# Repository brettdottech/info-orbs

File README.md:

# Info Orbs — Widget Expansion (Simon Geiger's fork)

This is a personal fork of [brettdottech/info-orbs](https://github.com/brettdottech/info-orbs), an open source ESP32-based desk display with five round TFT screens ("orbs"). This fork adds new widgets on top of the upstream project — currently a **Calendar widget** (see below).

> This fork isn't affiliated with or supported by the upstream project's Discord/community — please only reach out there for questions about the base hardware/firmware, not for issues specific to the widgets added here.

## Getting the hardware & base setup

This fork doesn't change the hardware or the base setup process, so refer to the upstream project for all of that:

- [Get a Dev Kit](https://brett.tech/collections/electronics-projects/products/info-orbs-full-dev-kit) — all the parts you need, pre-picked.
- [Firmware Install / Flashing Guide](references/Firmware%20Install%20Guide.md) and [YouTube assembly/flashing walkthrough](https://link.brett.tech/orbsYT).
- [Upstream README](https://github.com/brettdottech/info-orbs) — wiring diagram, dev environment (PlatformIO) setup, and the full list of existing widgets (clock, weather, stocks, MQTT, parqet.com, custom web data) and their configuration.
- [Discord](https://link.brett.tech/discord) for general project support and community.

Once you have the base project cloned, built, and flashing successfully (per the guides above), come back here for the widgets this fork adds.

## Calendar Widget

Shows your calendar right on the orbs: a clock, a month-at-a-glance grid, and an agenda of upcoming events — synced from any calendar that can publish a standard `.ics` feed (Google Calendar, Outlook/Microsoft 365, iCloud, etc.).

<!-- TODO: add a photo of the calendar widget in action -->

**What it brings you:**
- **Orb 1 — Clock.** Reuses the existing clock widget.
- **Orb 2 — Month grid.** Current month, today highlighted, with an indicator showing how long ago the calendar last synced.
- **Orbs 3–5 — Agenda**, toggleable between two modes:
  - *Next 3 events* — your next few upcoming events, title + time.
  - *Next 3 days* — a day-by-day view of what's coming up, several events per day.
  - An event that's currently happening is highlighted with a ring so it's obvious at a glance.
- Recurring events are supported (daily/weekly/monthly/yearly patterns, including things like "2nd Wednesday of the month"), including individually-rescheduled or cancelled occurrences.
- Declined and cancelled events are automatically filtered out.
- Calendars authored in a different timezone than your device convert correctly for a curated set of common named timezones (see limitations below).

**Setup:**
1. Get a secret `.ics` URL from your calendar provider (in Google Calendar: Settings → your calendar → "Secret address in iCal format"; Outlook: Settings → Shared calendars → "Publish a calendar"). Treat this URL like a password — anyone with it can read your calendar.
2. In `firmware/config/config.h` (see the upstream setup guide for how to create this file from `config.h.template`), set:
   ```c
   #define CALENDAR_ICS_URL "https://your-calendar-provider.example/your-secret-feed.ics"
   ```
3. Optionally raise `CALENDAR_MAX_EVENTS` (default 40) if you have a busy calendar and want more upcoming events kept in memory:
   ```c
   #define CALENDAR_MAX_EVENTS 80
   ```
4. Flash as usual. The calendar syncs automatically at boot and every hour after that.

**Using it:**
- Middle short press — switch between page 1/2 of the current agenda mode.
- Middle medium press — switch orbs 3–5 between "Next 3 events" and "Next 3 days".
- Middle long press — force an immediate re-sync of the calendar.
- Left/right — cycle to other widgets, same as everywhere else.

**Known limitations:** 
- a single `.ics` source at a time; 
- timezones are handled correctly for a curated list of common named zones (not full `VTIMEZONE`-block parsing — see [ADR-001](docs/adr/ADR-001-calendar-widget.md) for the exact scope and rationale, and for anyone wanting the full technical design behind this widget). 
- only been verified against Google Calendar and Outlook/Microsoft 365 `.ics` feeds so far — feedback on other providers (iCloud, etc.) is very welcome.

## Changelog

Notable changes in this fork (current version: **1.2.0**) are tracked in [CHANGELOG.md](CHANGELOG.md).

## License

This project (including this fork's additions) is licensed under AGPLv3 — see [LICENSE.txt](LICENSE.txt).

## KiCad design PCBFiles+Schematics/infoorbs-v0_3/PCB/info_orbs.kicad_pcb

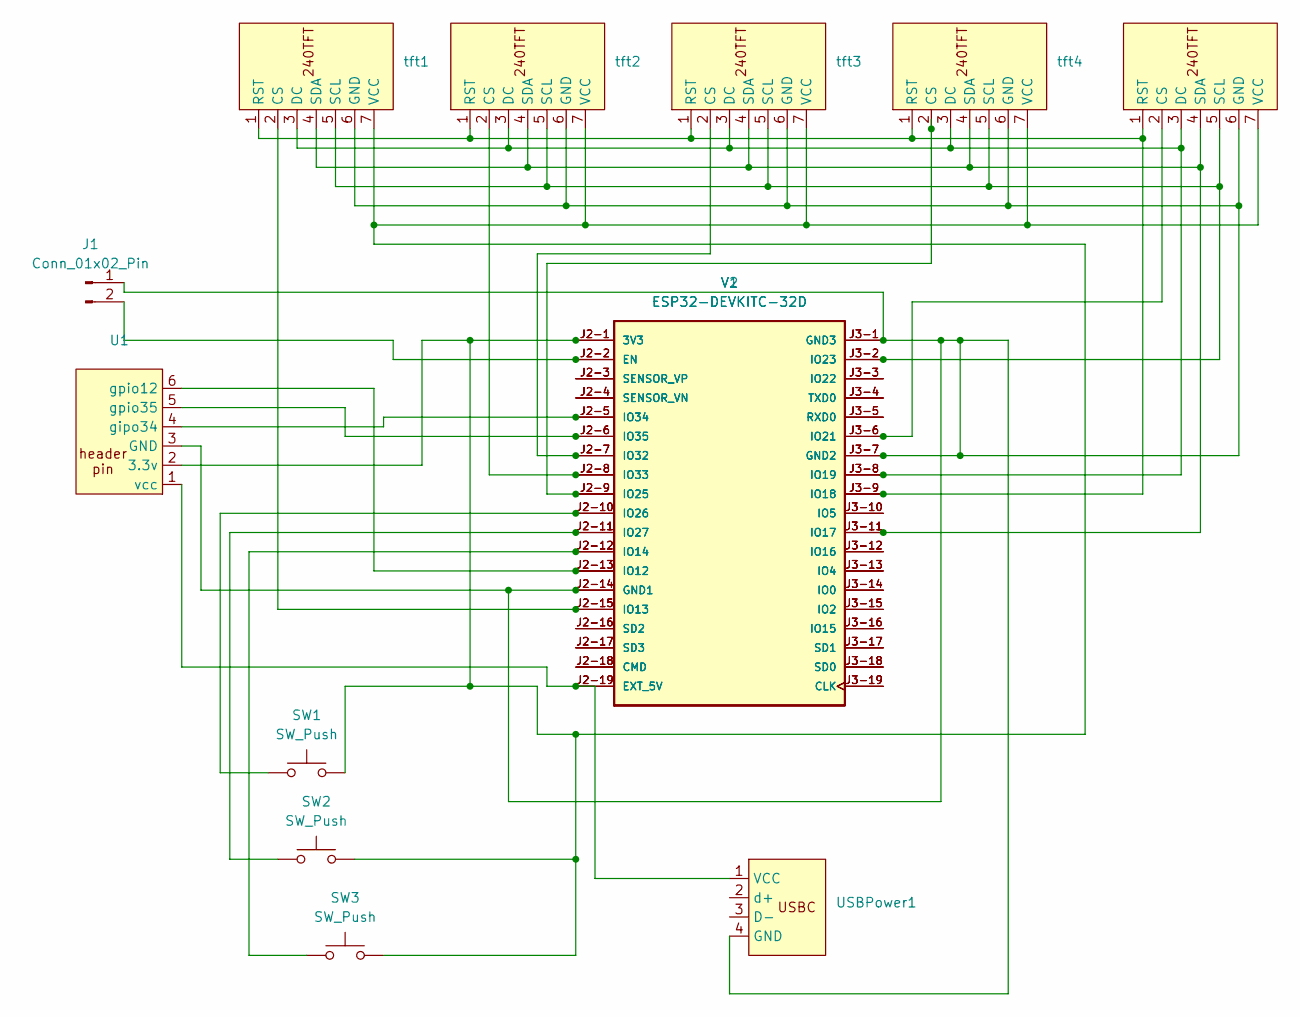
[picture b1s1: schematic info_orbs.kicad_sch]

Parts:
J1: Conn_01x02_Pin; PinHeader_1x02_P2.54mm_Vertical
SW1, SW2, SW3: SW_Push; SW_PUSH_6mm_H5mm
U1: PinHeader_1x06_P2.54mm_Vertical
USBPower1: PinHeader_1x04_P2.54mm_Vertical
V1: ESP32-DEVKITC-32D; 38 Pin Board; PARTREV V4
V2: ESP32-DEVKITC-32D; 38 Pin Board thin; PARTREV V4
tft1, tft2, tft3, tft4, tft5: PinHeader_1x07_P2.54mm_Vertical

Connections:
unnamed: J1.1, U1.3 (GND), USBPower1.4 (GND), V1.J2-14 (GND1), V1.J3-1 (GND3), V1.J3-7 (GND2), V2.J2-14 (GND1), V2.J3-1 (GND3), V2.J3-7 (GND2), tft1.6 (GND), tft2.6 (GND), tft3.6 (GND), tft4.6 (GND), tft5.6 (GND)
unnamed: J1.2, V1.J2-2 (EN), V2.J2-2 (EN)
unnamed: SW1.2, SW2.2, SW3.2, U1.2 (3.3v), V1.J2-1 (3V3), V2.J2-1 (3V3), tft1.7 (VCC), tft2.7 (VCC), tft3.7 (VCC), tft4.7 (VCC), tft5.7 (VCC)
unnamed: U1.4 (gipo34), V1.J2-5 (IO34), V2.J2-5 (IO34)
unnamed: U1.6 (gpio12), V1.J2-13 (IO12), V2.J2-13 (IO12)
unnamed: U1.5 (gpio35), V1.J2-6 (IO35), V2.J2-6 (IO35)
unnamed: U1.1 (vcc), USBPower1.1 (VCC), V1.J2-19 (EXT_5V), V2.J2-19 (EXT_5V)
unnamed: V1.J3-19 (CLK), V2.J3-19 (CLK)
unnamed: V1.J2-18 (CMD), V2.J2-18 (CMD)
unnamed: V1.J3-14 (IO0), V2.J3-14 (IO0)
unnamed: V1.J3-15 (IO2), V2.J3-15 (IO2)
unnamed: V1.J3-13 (IO4), V2.J3-13 (IO4)
unnamed: V1.J3-10 (IO5), V2.J3-10 (IO5)
unnamed: V1.J2-15 (IO13), V2.J2-15 (IO13), tft1.2 (CS)
unnamed: SW3.1, V1.J2-12 (IO14), V2.J2-12 (IO14)
unnamed: V1.J3-16 (IO15), V2.J3-16 (IO15)
unnamed: V1.J3-12 (IO16), V2.J3-12 (IO16)
unnamed: V1.J3-11 (IO17), V2.J3-11 (IO17), tft1.4 (SDA), tft2.4 (SDA), tft3.4 (SDA), tft4.4 (SDA), tft5.4 (SDA)
unnamed: V1.J3-9 (IO18), V2.J3-9 (IO18), tft1.1 (RST), tft2.1 (RST), tft3.1 (RST), tft4.1 (RST), tft5.1 (RST)
unnamed: V1.J3-8 (IO19), V2.J3-8 (IO19), tft1.3 (DC), tft2.3 (DC), tft3.3 (DC), tft4.3 (DC), tft5.3 (DC)
unnamed: V1.J3-6 (IO21), V2.J3-6 (IO21), tft5.2 (CS)
unnamed: V1.J3-3 (IO22), V2.J3-3 (IO22)
unnamed: V1.J3-2 (IO23), V2.J3-2 (IO23), tft1.5 (SCL), tft2.5 (SCL), tft3.5 (SCL), tft4.5 (SCL), tft5.5 (SCL)
unnamed: V1.J2-9 (IO25), V2.J2-9 (IO25), tft4.2 (CS)
unnamed: SW1.1, V1.J2-10 (IO26), V2.J2-10 (IO26)
unnamed: SW2.1, V1.J2-11 (IO27), V2.J2-11 (IO27)
unnamed: V1.J2-7 (IO32), V2.J2-7 (IO32), tft3.2 (CS)
unnamed: V1.J2-8 (IO33), V2.J2-8 (IO33), tft2.2 (CS)
unnamed: V1.J3-5 (RXD0), V2.J3-5 (RXD0)
unnamed: V1.J3-18 (SD0), V2.J3-18 (SD0)
unnamed: V1.J3-17 (SD1), V2.J3-17 (SD1)
unnamed: V1.J2-16 (SD2), V2.J2-16 (SD2)
unnamed: V1.J2-17 (SD3), V2.J2-17 (SD3)
unnamed: V1.J2-4 (SENSOR_VN), V2.J2-4 (SENSOR_VN)
unnamed: V1.J2-3 (SENSOR_VP), V2.J2-3 (SENSOR_VP)
unnamed: V1.J3-4 (TXD0), V2.J3-4 (TXD0)

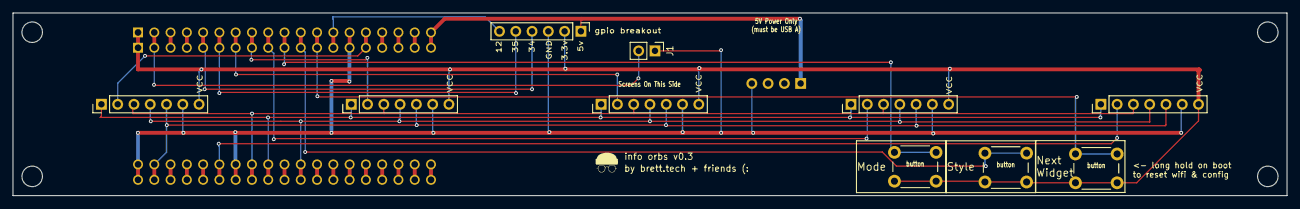
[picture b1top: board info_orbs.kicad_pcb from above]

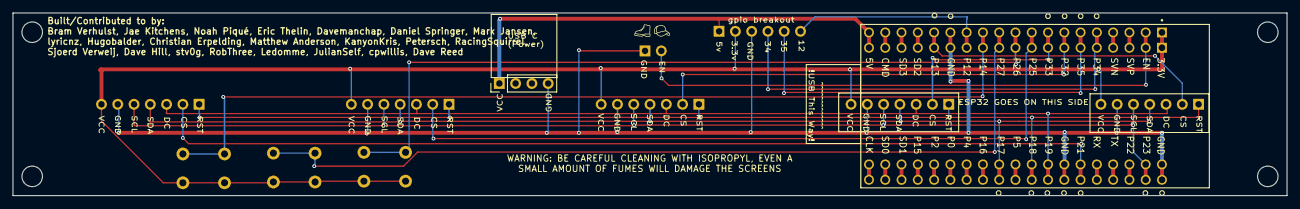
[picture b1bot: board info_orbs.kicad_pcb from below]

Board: 2 copper layers, 198.8 x 28.5 mm, 14 parts (3 on the bottom side), 36 nets.

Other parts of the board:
G*: LOGO; beaniegraphioc

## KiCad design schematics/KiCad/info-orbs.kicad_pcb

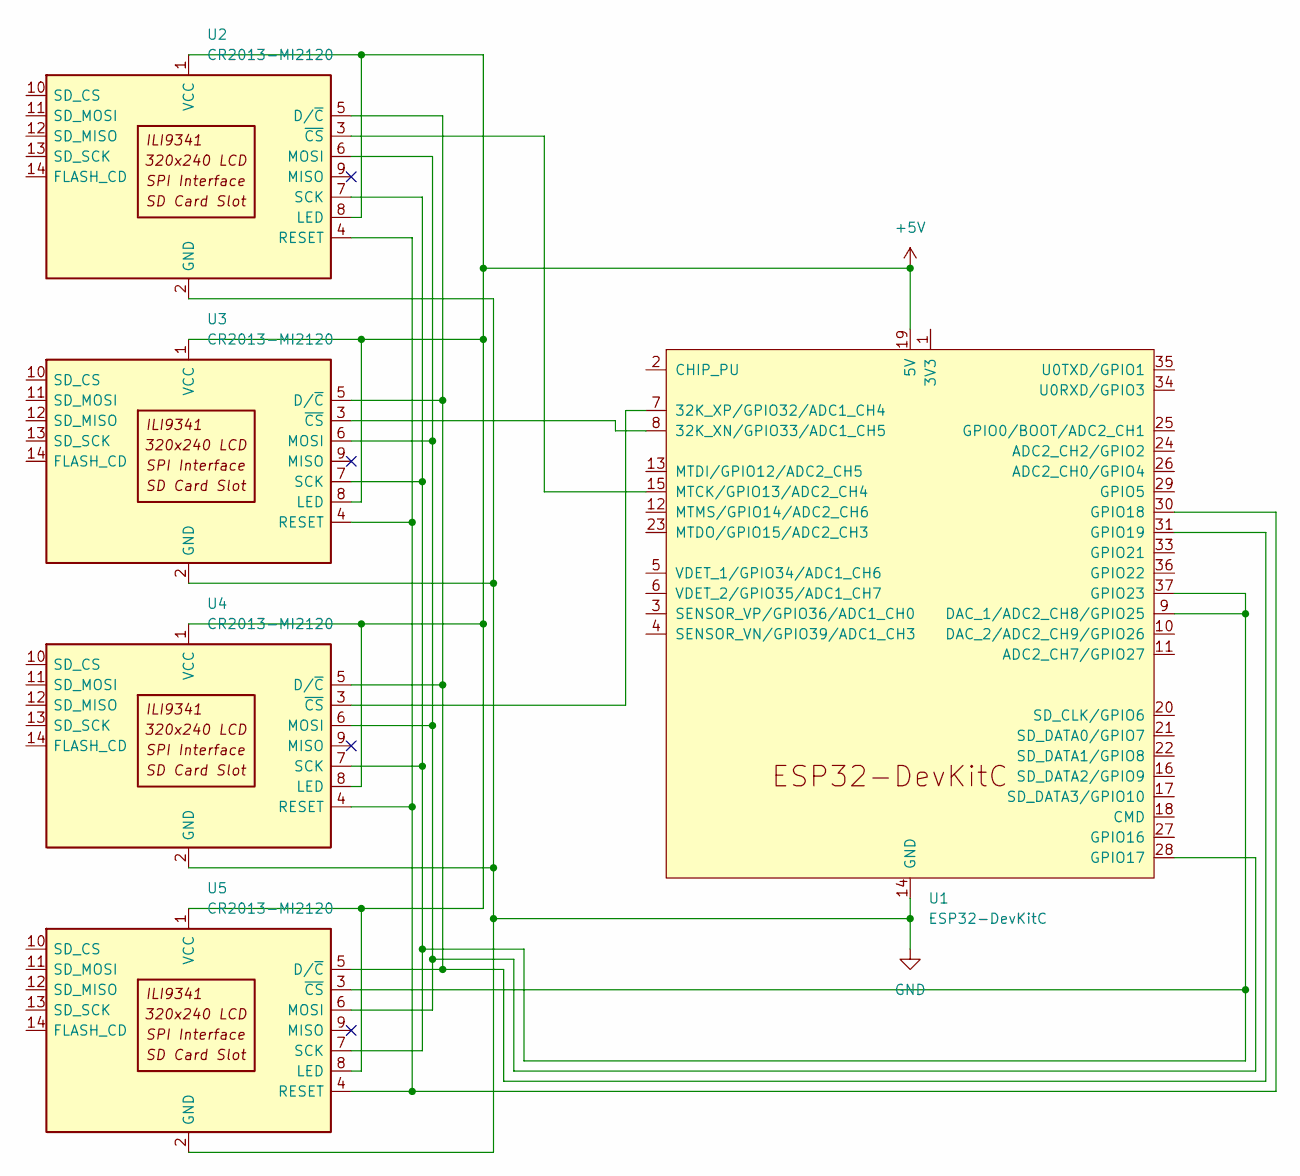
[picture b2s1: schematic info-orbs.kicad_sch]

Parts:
U1: ESP32-DevKitC
U2, U3, U4, U5: CR2013-MI2120

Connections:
+5V: U1.19 (5V), U2.1 (VCC), U2.8 (LED), U3.1 (VCC), U3.8 (LED), U4.1 (VCC), U4.8 (LED), U5.1 (VCC), U5.8 (LED)
GND: U1.14 (GND), U1.32 (GND), U1.38 (GND), U2.2 (GND), U3.2 (GND), U4.2 (GND), U5.2 (GND)
unnamed: U1.8 (32K_XN/GPIO33/ADC1_CH5), U3.3 (~CS)
unnamed: U1.7 (32K_XP/GPIO32/ADC1_CH4), U4.3 (~CS)
unnamed: U1.9 (DAC_1/ADC2_CH8/GPIO25), U1.37 (GPIO23), U2.7 (SCK), U3.7 (SCK), U4.7 (SCK), U5.3 (~CS), U5.7 (SCK)
unnamed: U1.28 (GPIO17), U2.6 (MOSI), U3.6 (MOSI), U4.6 (MOSI), U5.6 (MOSI)
unnamed: U1.30 (GPIO18), U2.4 (RESET), U3.4 (RESET), U4.4 (RESET), U5.4 (RESET)
unnamed: U1.31 (GPIO19), U2.5 (D/~C), U3.5 (D/~C), U4.5 (D/~C), U5.5 (D/~C)
unnamed: U1.15 (MTCK/GPIO13/ADC2_CH4), U2.3 (~CS)

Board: 2 copper layers, 5 parts (0 on the bottom side), 9 nets, no tracks yet.

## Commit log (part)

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2024-12-15 Added stock list from StockWidget to WebPortal
2024-12-15 Added TFT brightness, nightmode and widget cycling
2024-12-15 Added mDNS for testing
2024-12-15 typo
2024-12-15 Added getConfig{String|Int|Float} and fixed clockFormat
2024-12-15 Text
2024-12-15 Add length option to addConfigString()
2024-12-15 Added invertedOrbs and changed some texts
2024-12-15 Make TIMEZONE_API_LOCATION configurable
2024-12-15 Removed unused function
2024-12-15 Added custom "Buttons" menu to WebPortal, removed "Update"
2024-12-15 Fixed MQTT compile problem
2024-12-15 Added config to MQTT. Added INCLUDE_* defines.
2024-12-15 Added option for MEMORY_DEBUG
2024-12-15 reuse rawStream
2024-12-15 renamed setupWiFiManager to setupWebPortal in CM
2024-12-15 rotate display earlier
2024-12-15 Added SHOW_MEMORY_USAGE macro
2024-12-15 Removing #ifdef from widget #include in main (not necessary)
2024-12-15 Cleanup
2024-12-15 Reordered widgets
2024-12-15 [MegaLinter] Apply linters fixes
2024-12-15 Move more debug to PARQET_DEBUG_PRINT
2024-12-15 Made mDNS optional
2024-12-15 Set format24hour correctly, fixes #175
2024-12-15 Reduced TTF cache size to save a bit of memory
2024-12-15 Added define check for OrbsWiFiManager
2024-12-15 Change includes to "OrbsWiFiManager.h"
2024-12-15 Configure ClockType in WebPortal
2024-12-15 Debug for Parqet
2024-12-15 Changed imports
2024-12-15 Let's try something else to fix #168
2024-12-15 Improvements after review
2024-12-15 .setCacheSize comment
2024-12-15 Added Parqet default timeframe to WebPortal
2024-12-15 Clarify
2024-12-15 Style the WebPortal /params a bit nicer
2024-12-15 Moved pseudo parameters to static vars
2024-12-15 NTP server can be configured in WebPortal
2024-12-15 String literals
2024-12-15 Improved WebPortal style
2024-12-15 Added git branch to Welcome screen (if not main)
2024-12-15 yml fix
2024-12-15 Remove debug output
2024-12-17 Dynamic embedding is now possible (and just a bit hacky)
2024-12-17 updates THANKS.md
2024-12-17 Clarification in .py embed script
2024-12-17 Now clock faces
2024-12-17 Added cache and optimizations for colorize
2024-12-20 Fixed clear on boot buttons
2024-12-21 use enum
2024-12-21 Clear LittleFS dir, Added script comments
2024-12-21 Removed old clock-custom.*
2024-12-21 Custom Clocks now live in LittleFS
2024-12-21 Added NixieVariants enum
2024-12-21 CustomClock README.md
2024-12-21 downloadFromUrl
2024-12-21 Support images from GitHub
2024-12-21 Changed to make the weather feed plugable. Also added a feed for Tempest personl weather stations
2024-12-21 another fix
2024-12-22 Revert size of seconds indicator
    Previous commit unintentionally included a larger seconds indicator. This commit reverts it back to the original size.
2024-12-23 Use AJAX for fetchFromUrl
2024-12-23 Added bullet points to dirs
2024-12-23 Added Browse Filesystem to Menu
2024-12-23 Remove alert after upload
2024-12-23 Added drop area for uploads
2024-12-23 Use modulus function instead of IF statements.
    Replaced "IF > 360, -360" logic with modulus 360 on original calcs. Thanks Che!
2024-12-23 updated comment
2024-12-24 Added an option to enable/disable custom clocks
2024-12-27 Drawscript- simple line based script to generate widget drawing code server-side
2024-12-28 Make High/Low interval configurabl
2024-12-28 tweak debug prints
2024-12-29 Parqet: Fixed duplicate config keys
2024-12-30 fixed memory leak regarding HTTPClient and WiFiClientSecure not cleaning up after task completion. Added an option to pass a preProcessResponse callback to apply json filters or other tasks to prepar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
2024-12-31 semaphore optimations
2024-12-31 Init buttons first
2024-12-31 Move check for empty url to the top
2024-12-31 move taskSemaphore to a GlobalResources.cpp where it can be referenced and used elsewhere. Also add comments/docs on taskSemaphore usage
2025-01-02 Define HIGHLOW Interval if missing in config.h
2025-01-02 Don't block when trying to connect to mqtt server
2025-01-03 Show Stock change as Price or Percent
    Option added to switch between percent or price change for stocks.
2025-01-04 Add Filp ClockFace
2025-01-05 Remove APPLY_FIXES_MODE (always use "commit")
2025-01-05 Remove APPLY_FIXES_EVENT (always use "all")
2025-01-05 Bump Arduino version to 2.0.17
2025-01-06 Fixes a small bug in the WebDataElementCircleParser for the 'filled' field as it was checking for an integer value, where instead it should be looking for a boolean.
2025-01-06 add a MEMORY_DEBUG_INTERVAL to specify the frequency of memory debug update
2025-01-06 update approach slightly
2025-01-06 fixed issue where no config specified
2025-01-06 rename
2025-01-07 fixes
2025-01-07 clang-format
2025-01-07 restored coments
2025-01-07 more cleanup of git commits
2025-01-07 implement ArduinioLog
2025-01-07 changed variable name
2025-01-09 Change Feeds to use std::map
2025-01-09 Rename!
2025-01-10 renamed http methods. added error logging. changed task modules to use Log prints instead of Serial.print
2025-01-10 readded docs file with revisions to remove internal methods
2025-01-16 Refine JSON filter and update portfolio value handling.
    Updated the JSON deserialization filter to include more precise fields for holdings and performance metrics. Adjusted how portfolio values are processed to align with the refined filter structure for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
2025-01-28 Added new Clocktype Flipclock with animation
    Real Flipclock animation supporting 12h/24h modes
2025-01-28 Convert currencySymbol to Uppercase
    In case twelvedata sends the currency like for the Stock BARC as GBp instead of GBP the currency will not display. Before comparing the currency will be converted to uppercase.
2025-02-14 Reduced size of flipclock images
2025-02-18 Add new filters and normalize asset type for comparison
    Added "shares" and "isSold" filters to holdings for better data handling. Ensured asset type is converted to lowercase before comparison to prevent case-sensitivity issues.
    skip fix
2025-02-23 ParqetWidget now uses a proxy for less memory usage and faster parsing
    Added support for new performance metrics and charts. Simplified HTTP request handling using TaskFactory and migrated response processing logic. Introduced a proxy URL configuration and replaced perc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
2025-02-23 Refactor task naming and simplify asset type logic.
    Updated task-related log messages for clarity and replaced asset type filtering logic with a simplified approach. Removed unused checks for "security" or "crypto" assets, ensuring all holdings are pr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
2025-02-23 Simplify portfolio ID handling in updatePortfolio.
    Replaced redundant string conversions with direct usage of `m_portfolioId`. This improves code readability and slightly optimizes performance by avoiding unnecessary object construction.
2025-02-23 Rename "perf" to "performance" for clarity and consistency.
    Replaced "perf" with "performance" across method names, variables, and comments to improve code readability and align naming with descriptive standards. Also updated "m_parquetProxyUrl" to "m_proxyUr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
2025-02-23 Remove unused functions from ParqetWidget.h
    Deleted `updatePortfolioChart` and `processResponseChart` as they are no longer referenced or required. This cleanup improves code readability and reduces potential maintenance overhead.
2025-02-25 Added PCB dimensions
2025-02-25 Set default language fallback and refine translation loading.
    Updated I18n system to handle a default language fallback when loading translations, ensuring robust behavior when specific language files are unavailable. Renamed parameters and improved clarity in 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
2025-02-25 Add internationalization (i18n) support with language files
    Introduced an i18n system for localizing app text using key-value language files. Added `I18n.h` and `I18n.cpp` to manage translations, integrated i18n into welcome screens, and updated `MainHelper` 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
2025-02-25 Add multi-language support with language selection
    Introduce language selection using a dropdown in the configuration settings, replacing hardcoded default handling. Added support for managing language IDs, retrieving available languages, and loading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
2025-02-25 Fix navigation logic in WidgetSet::prev()
    Adjusted the decrement logic in WidgetSet::prev() to prevent accessing invalid widget indices. Ensures proper wrapping behavior when navigating to the previous widget in the circular widget list.
2025-02-25 Refactor I18n handling and enhance WidgetSet functionality
    Introduced dynamic widget-specific translations and centralized language management in I18n. Added helper methods in WidgetSet for widget retrieval and improved iteration logic. This lays groundwork 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
2025-02-25 Refactor i18n strings and enhance logging for translations.
    Updated i18n keys for consistency and improved translation handling. Added logging for missing and found translations in `I18n::get`. Simplified configuration translations using the `i18n` helper met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
2025-02-25 **Refactor i18n implementation and restructure translations**
    Replaced hardcoded strings with i18n keys across various modules to improve translations consistency and maintainability. Introduced dedicated translation files for better organization, including new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
2025-02-25 Removed old .txt i18n files from copy_files_to_littlefs.py
2025-02-25 Refactor translations to use custom type for cleaner syntax
    Replaced raw translation array declarations with `Translation` and `TranslationMulti` typedefs to improve readability and maintainability. Updated all translation-related headers and source files to 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
2025-02-26 Add validation for language ID in I18n::setLanguageId
    Ensure the language ID is within valid bounds before assignment. If the provided ID is invalid, default to the predefined language to prevent unexpected behavior.
2025-02-28 allow default pin assignments to be overridden in platformio if needed. Also removed #undef TFT_X settings as these would undefine any corresponding pins defined in the platformio build_flag section.
2025-02-28 Refactor TFT config and add new translations
    Updated TFT rotation configuration to dynamically handle options via `i18nMultiStr` for improved flexibility. Added new translation constants for "high", "low", "screen mode", "temperature units", an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
2025-02-28 Add i18n support for StockWidget
    Integrated internationalization (i18n) into StockWidget by introducing translation variables for key strings. This update allows easier adaptation to multiple languages and improves readability by ce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
2025-02-28 Add i18n support for MQTTWidget configuration fields
    Integrated internationalization (i18n) by introducing `MQTTTranslations.h` and `MQTTTranslations.cpp`. Updated the MQTTWidget configuration fields to use translatable strings for better localization 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
2025-02-28 Fix include case for I18n.h in translation headers
    Updated the include directive to use the correct capitalization for "I18n.h" in ClockTranslations.h and MQTTTranslations.h. This ensures consistency and avoids potential case-sensitivity issues on ce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
2025-03-01 Set NTP update interval to every 15 minutes. Also check for update returned unixEpoch year and ensure its within a defined range and it its not retry every 3 seconds until its a valid return. should 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
2025-03-01 some cleanup of serial monitor output
2025-03-01 On initial load show loading data messge so user doesnt have to look at blank displays
2025-03-02 reduced font size of message
2025-03-02 update m_secondTimerPrev to millis() so that the function only gets executed once a second
2025-03-02 Refactor configuration methods to support translation objects
    Updated configuration methods across multiple widgets to accept
    Translation objects directly, streamlining the i18n logic. This change
    reduces redundancy and improves code readability by consolidating
    localization handling in the ConfigManager.
2025-03-02 fixed previous update
2025-03-02 moved the clearing code and used the SERIAL_INTERFACE_INIT_DELAY value to set the delay
2025-07-18 Implement automatic dimming capability for photoresistor on gpio34
